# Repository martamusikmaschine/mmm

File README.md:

# Marta Musik Maschine
Before doing anything, checkout the associated blog post series at [martamusikmaschine.com](https://martamusikmaschine.com).

Marta Musik Maschine is a DIY, RFID enabled, multi-purpose, audio and light device for kids. It's open source and you can build one yourself. It's not hard at all, I promise.

This repository contains all the code needed on the Raspberry Pi, a KiCad project that enables you to etch/order a PCB and a few stl models that you can print on a 3D printer.

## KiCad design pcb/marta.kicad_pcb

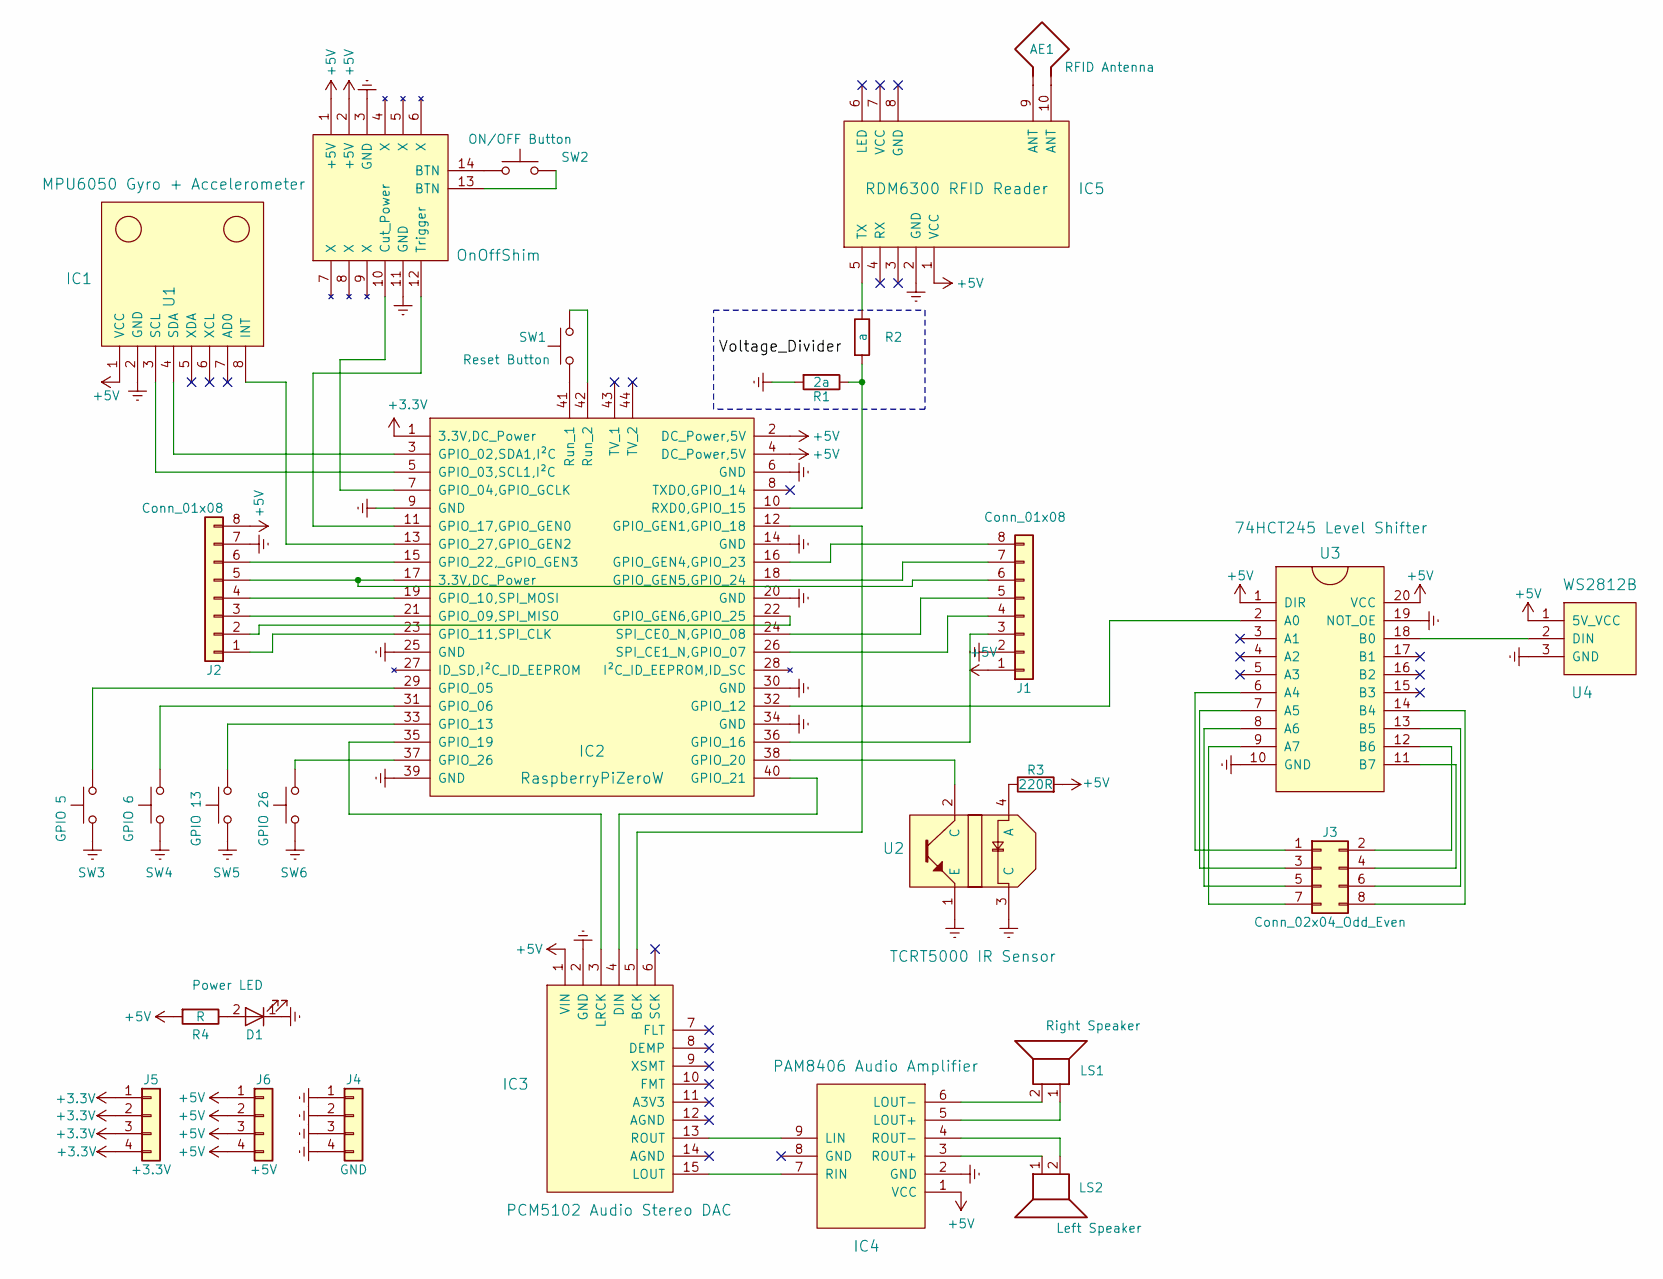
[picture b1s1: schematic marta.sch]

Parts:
AE1: RFID Antenna; JST_XH_B02B-XH-A_02x2.50mm_Straight
D1: Power LED; JST_XH_B02B-XH-A_02x2.50mm_Straight
IC1: MPU6050 Gyro + Accelerometer; MPU6050
IC2: RaspberryPiZeroW; RaspberryPiZeroW_UpSideDown
IC3: PCM5102 Audio Stereo DAC; PCM5102
IC4: PAM8406 Audio Amplifier; PAM8406
IC5: RDM6300 RFID Reader; RDM6300
J1, J2: Conn_01x08; JST_XH_B08B-XH-A_08x2.50mm_Straight
J3: Conn_02x04_Odd_Even; Pin_Header_Straight_2x04_Pitch2.54mm
J4: GND; Pin_Header_Straight_1x04_Pitch2.54mm
J5: +3.3V; Pin_Header_Straight_1x04_Pitch2.54mm
J6: +5V; Pin_Header_Straight_1x04_Pitch2.54mm
LS1: Right Speaker; JST_XH_B02B-XH-A_02x2.50mm_Straight
LS2: Left Speaker; JST_XH_B02B-XH-A_02x2.50mm_Straight
R1: 2a; R_Axial_DIN0207_L6.3mm_D2.5mm_P10.16mm_Horizontal
R2: a; R_Axial_DIN0207_L6.3mm_D2.5mm_P10.16mm_Horizontal
R3: 220R; R_Axial_DIN0207_L6.3mm_D2.5mm_P10.16mm_Horizontal
R4: R; R_Axial_DIN0207_L6.3mm_D2.5mm_P10.16mm_Horizontal
SW1: Reset Button; JST_XH_B02B-XH-A_02x2.50mm_Straight
SW2: ON/OFF Button; JST_XH_B02B-XH-A_02x2.50mm_Straight
SW3: GPIO 5; JST_XH_B02B-XH-A_02x2.50mm_Straight
SW4: GPIO 6; JST_XH_B02B-XH-A_02x2.50mm_Straight
SW5: GPIO 13; JST_XH_B02B-XH-A_02x2.50mm_Straight
SW6: GPIO 26; JST_XH_B02B-XH-A_02x2.50mm_Straight
U1: OnOffShim
U2: TCRT5000 IR Sensor; JST_XH_B04B-XH-A_04x2.50mm_Straight
U3: 74HCT245 Level Shifter; DIP-20_W7.62mm
U4: WS2812B; Pin_Header_Straight_1x03_Pitch2.54mm

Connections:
+3V3: IC2.1 (3.3V,DC_Power), J5.1, J5.2, J5.3, J5.4
+5V: IC1.1 (VCC), IC2.2 (DC_Power,5V), IC2.4 (DC_Power,5V), IC3.1 (VIN), IC4.1 (VCC), IC5.1 (VCC), J1.1, J2.8, J6.1, J6.2, J6.3, J6.4, R3.2, R4.2, U1.1 (+5V), U1.2 (+5V), U3.1 (DIR), U3.20 (VCC), U4.1 (5V_VCC)
GNDREF: D1.1 (K), IC1.2 (GND), IC2.6 (GND), IC2.9 (GND), IC2.14 (GND), IC2.20 (GND), IC2.25 (GND), IC2.30 (GND), IC2.34 (GND), IC2.39 (GND), IC3.2 (GND), IC4.2 (GND), IC5.2 (GND), J1.2, J2.7, J4.1, J4.2, J4.3, J4.4, R1.2, SW3.1, SW4.1, SW5.1, SW6.1, U1.3 (GND), U1.11 (GND), U2.1 (E), U2.3 (C), U3.10 (GND), U3.19 (NOT_OE), U4.3 (GND)
unnamed: AE1.1, IC5.9 (ANT)
unnamed: AE1.2, IC5.10 (ANT)
unnamed: D1.2 (A), R4.1
unnamed: IC1.3 (SCL), IC2.5 (GPIO_03,SCL1,I²C)
unnamed: IC1.4 (SDA), IC2.3 (GPIO_02,SDA1,I²C)
unnamed: IC1.8 (INT), IC2.13 (GPIO_27,GPIO_GEN2)
unnamed: IC2.7 (GPIO_04,GPIO_GCLK), U1.10 (Cut_Power)
unnamed: IC2.10 (RXD0,GPIO_15), R1.1, R2.2
unnamed: IC2.11 (GPIO_17,GPIO_GEN0), U1.12 (Trigger)
unnamed: IC2.12 (GPIO_GEN1,GPIO_18), IC3.5 (BCK)
unnamed: IC2.15 (GPIO_22,_GPIO_GEN3), J2.6
unnamed: IC2.16 (GPIO_GEN4,GPIO_23), J1.8
unnamed: IC2.17 (3.3V,DC_Power), J1.6, J2.5
unnamed: IC2.18 (GPIO_GEN5,GPIO_24), J1.7
unnamed: IC2.19 (GPIO_10,SPI_MOSI), J2.4
unnamed: IC2.21 (GPIO_09,SPI_MISO), J2.3
unnamed: IC2.22 (GPIO_GEN6,GPIO_25), J2.2
unnamed: IC2.23 (GPIO_11,SPI_CLK), J2.1
unnamed: IC2.24 (SPI_CE0_N,GPIO_08), J1.5
unnamed: IC2.26 (SPI_CE1_N,GPIO_07), J1.4
unnamed: IC2.29 (GPIO_05), SW3.2
unnamed: IC2.31 (GPIO_06), SW4.2
unnamed: IC2.32 (GPIO_12), U3.2 (A0)
unnamed: IC2.33 (GPIO_13), SW5.2
unnamed: IC2.35 (GPIO_19), IC3.3 (LRCK)
unnamed: IC2.36 (GPIO_16), J1.3
unnamed: IC2.37 (GPIO_26), SW6.2
unnamed: IC2.38 (GPIO_20), U2.2 (C)
unnamed: IC2.40 (GPIO_21), IC3.4 (DIN)
unnamed: IC2.41 (Run_1), SW1.1
unnamed: IC2.42 (Run_2), SW1.2
unnamed: IC3.13 (ROUT), IC4.9 (LIN)
unnamed: IC3.15 (LOUT), IC4.7 (RIN)
unnamed: IC4.3 (ROUT+), LS2.1
unnamed: IC4.4 (ROUT-), LS2.2
unnamed: IC4.5 (LOUT+), LS1.1
unnamed: IC4.6 (LOUT-), LS1.2
unnamed: IC5.5 (TX), R2.1
unnamed: J3.1, U3.6 (A4)
unnamed: J3.2, U3.12 (B6)
unnamed: J3.3, U3.7 (A5)
unnamed: J3.4, U3.11 (B7)
unnamed: J3.5, U3.8 (A6)
unnamed: J3.6, U3.13 (B5)
unnamed: J3.7, U3.9 (A7)
unnamed: J3.8, U3.14 (B4)
unnamed: R3.1, U2.4 (A)
unnamed: SW2.1, U1.14 (BTN)
unnamed: SW2.2, U1.13 (BTN)
unnamed: U3.18 (B0), U4.2 (DIN)

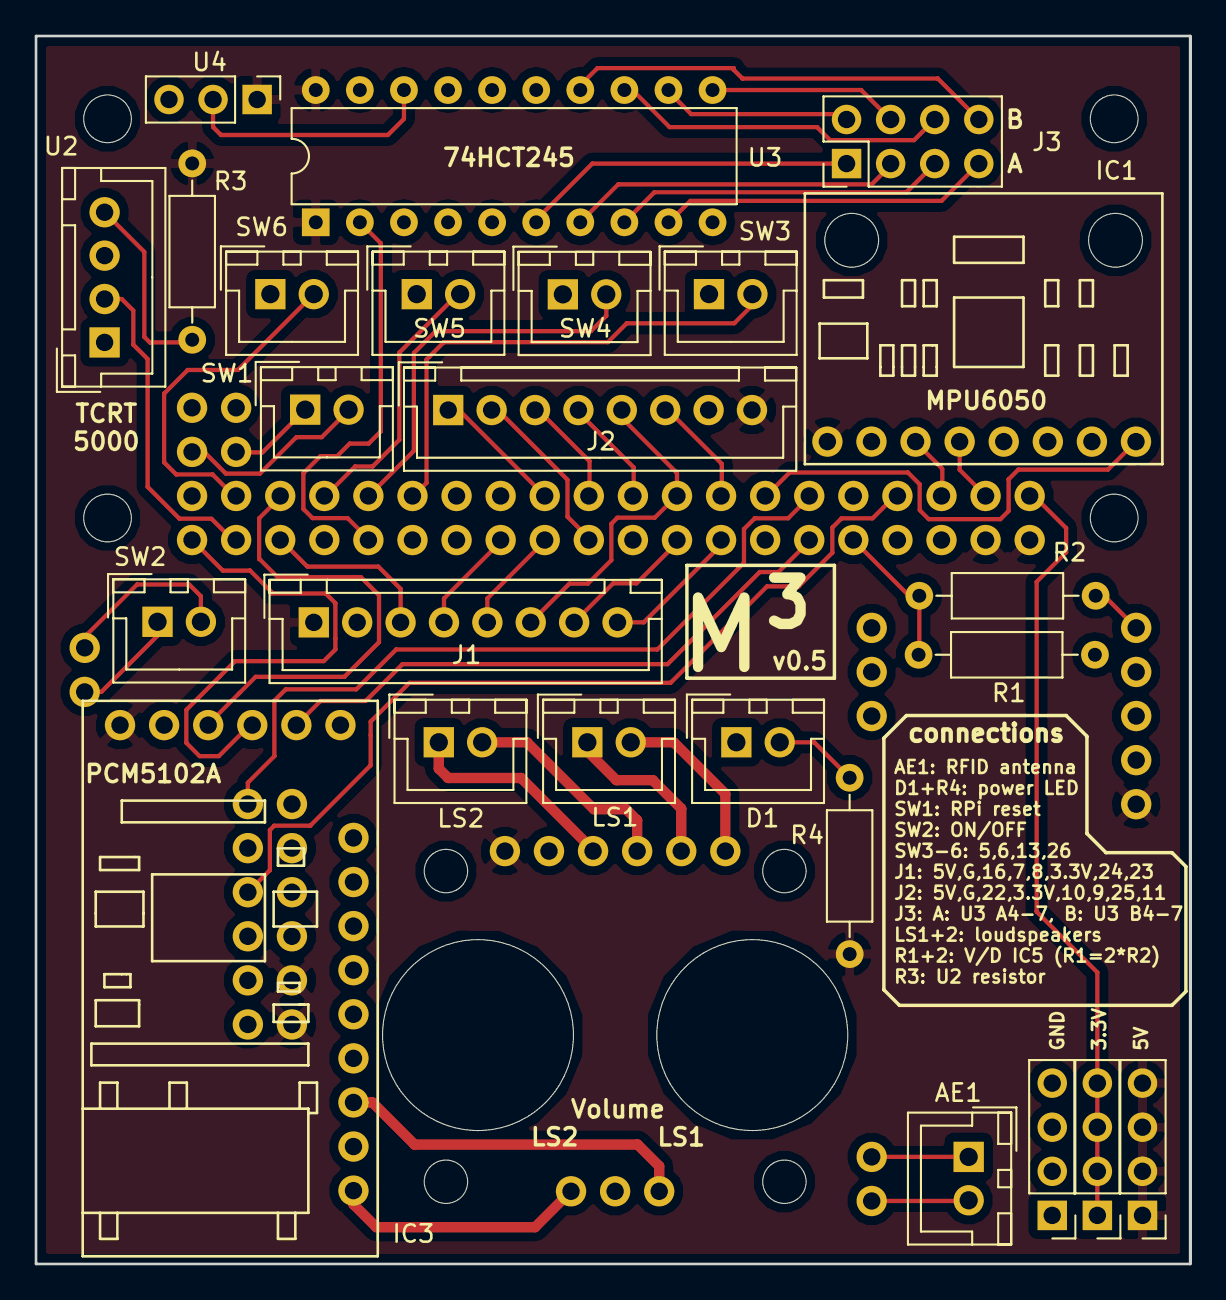
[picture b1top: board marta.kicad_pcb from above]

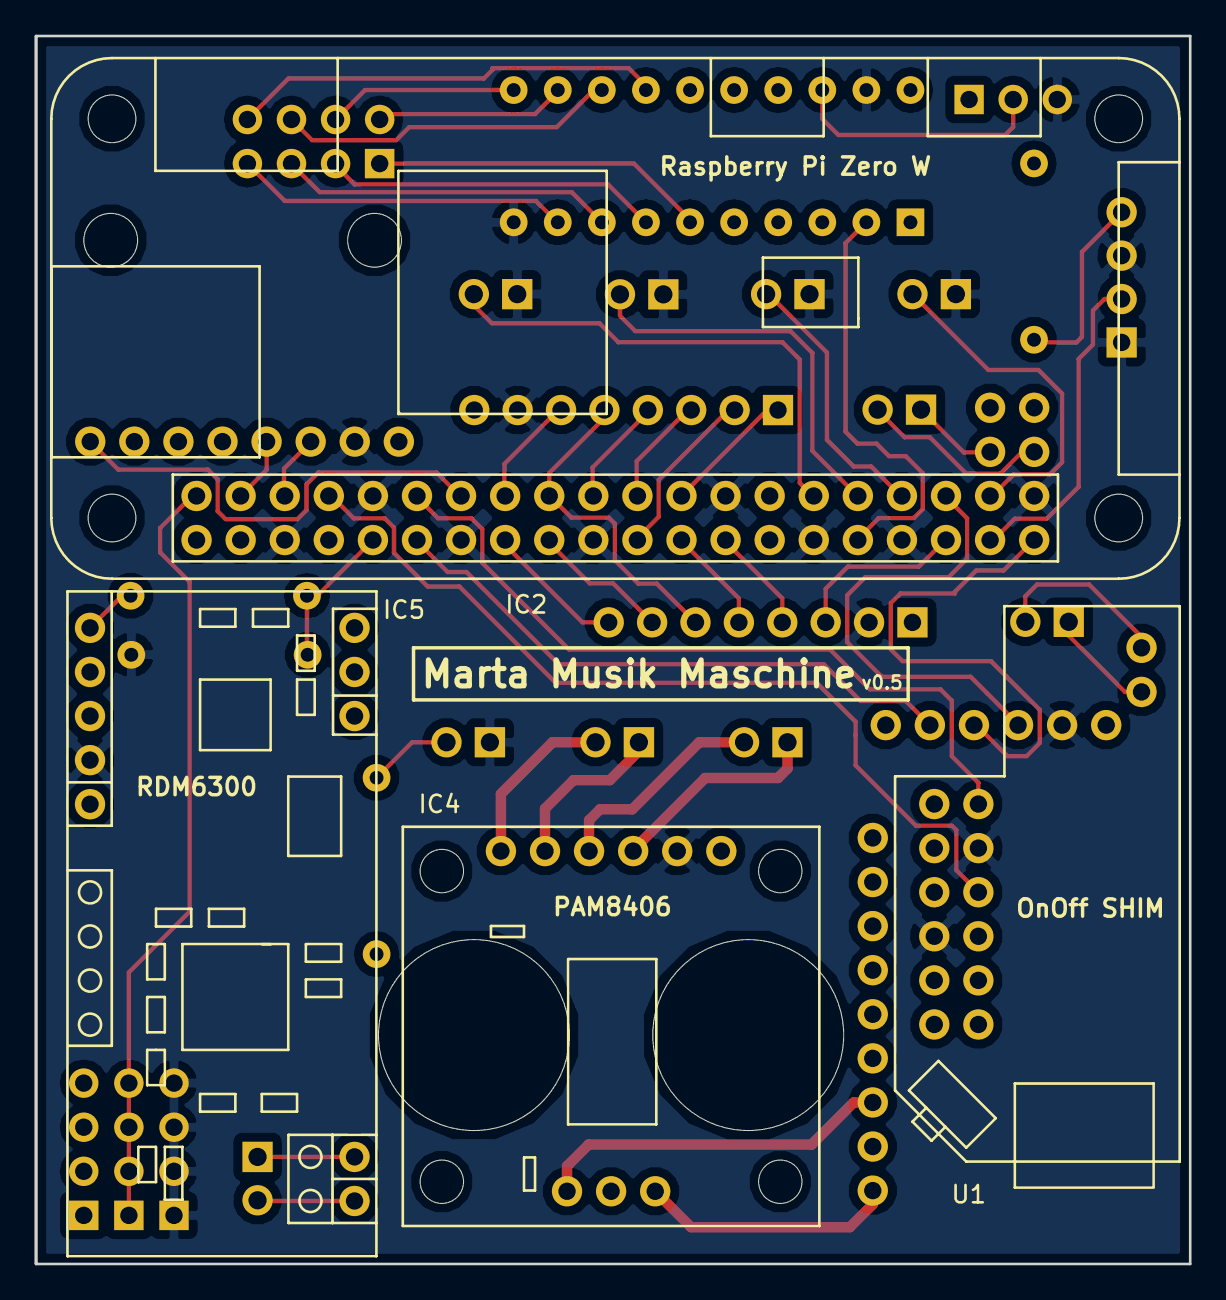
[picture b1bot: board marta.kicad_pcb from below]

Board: 2 copper layers, 66.5 x 70.8 mm, 29 parts (4 on the bottom side), 53 nets.

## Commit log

2019-03-10 init test
2019-03-10 init
2019-08-26 tried to cleanup all the files and dirs (#3)
2019-08-26 a the files (#4)
2019-08-27 Revise mpg123 (#5)
    * some comments, two timeouts
    * began to work on an error regarding non existing paths and on_error
    * renaming and refactoring.
2019-10-16 Error handling missing tag (#6)
    * ignore unknown tags in music handler
    * main functions and more
    * stuff
    * mre
    * changed the audio directory structure
    * debug exit on startup script
2019-10-16 cleanup script (#8)
2019-10-17 added gerber directory to gitignore
2019-10-30 readme update
2020-02-27 added a few iges and step files
